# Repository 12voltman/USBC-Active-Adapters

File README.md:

# USBC-Active-Adapters
Active USB-A adapters to USB-C, that don't break spec

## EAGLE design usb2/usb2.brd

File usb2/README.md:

A USB 2.0 only adapter from USB-A male to USB-C female with proper power control based on CC pins. Does not break spec like the passive adapters flooding the market.

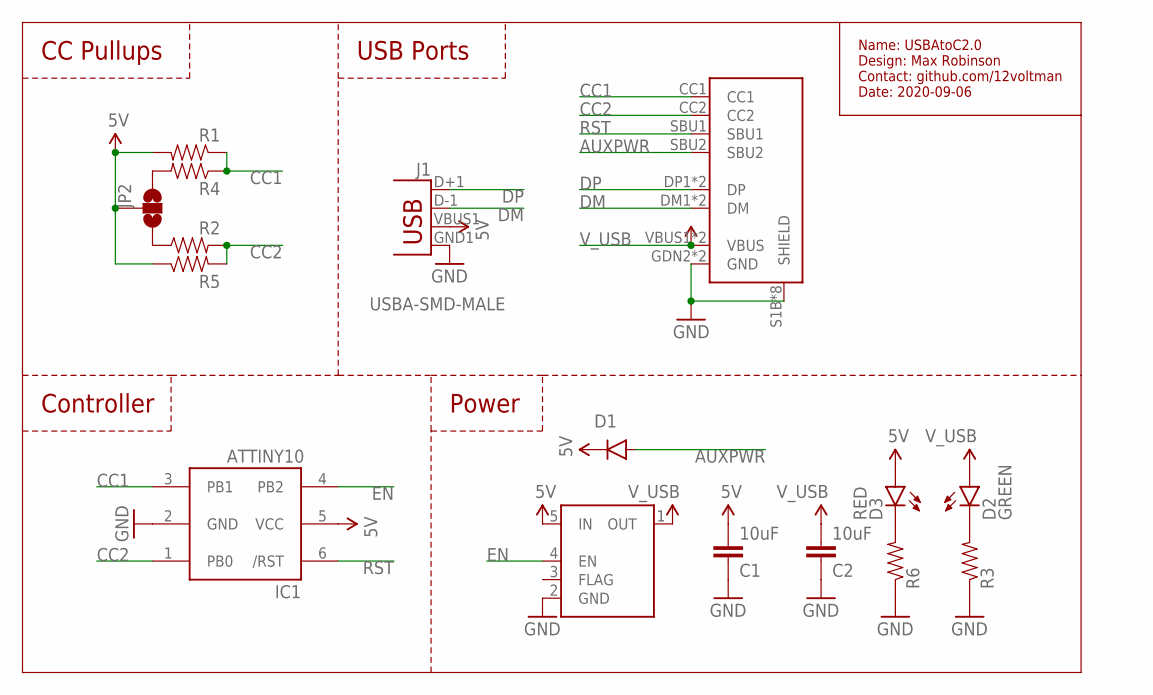
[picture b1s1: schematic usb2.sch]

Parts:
C1, C2: 10uF; 0603-CAP
D1: 250mA/100V; SOD-323
D2: GREEN; LED-0603
D3: RED; LED-0603
IC1: ATTINY10; SOT23-6
J1: USBA-SMD-MALE; USB-A-SMT-MALE
JP2: JUMPER-PAD-3-NOYES_SILK; PAD-JUMPER-3-NO_YES_SILK
R1, R2, R3, R4, R5, R6: RESISTOR0603; 0603-RES
U$1: USB-C_USB2ONLY-OUTLINE; USB-C_12PIN_HORZ-F-OUTLINE
U$2: AP22804/14*W5-7; SOT23-5

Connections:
5V: C1.2, D1.C, D3.A, IC1.5 (VCC), J1.VBUS1 (VBUS), JP2.2, R1.2, R5.1, U$2.5 (IN)
AUXPWR: D1.A, U$1.SBU2
CC1: IC1.3 (PB1), R1.1, R4.1, U$1.CC1
CC2: IC1.1 (PB0), R2.2, R5.2, U$1.CC2
DM: J1.D-1 (D-), U$1.DM1 (DM), U$1.DM2 (DM)
DP: J1.D+1 (D+), U$1.DP1 (DP), U$1.DP2 (DP)
EN: IC1.4 (PB2), U$2.4 (EN)
GND: C1.1, C2.1, IC1.2 (GND), J1.GND1 (GND), R3.1, R6.1, U$1.GDN2 (GND), U$1.GND1 (GND), U$1.S1B (SHIELD), U$1.S1T (SHIELD), U$1.S2B (SHIELD), U$1.S2T (SHIELD), U$1.S3B (SHIELD), U$1.S3T (SHIELD), U$1.S4B (SHIELD), U$1.S4T (SHIELD), U$2.2 (GND)
unnamed: D2.C, R3.2
unnamed: JP2.3, R2.1
unnamed: JP2.1, R4.2
unnamed: D3.C, R6.2
RST: IC1.6 (/RST), U$1.SBU1
V_USB: C2.2, D2.A, U$1.VBUS1 (VBUS), U$1.VBUS2 (VBUS), U$2.1 (OUT)

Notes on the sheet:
Controller
CC Pullups
USB Ports
Power
Name: USBAtoC2.0 Design: Max Robinson Contact: github.com/12voltman Date: 2020-09-06

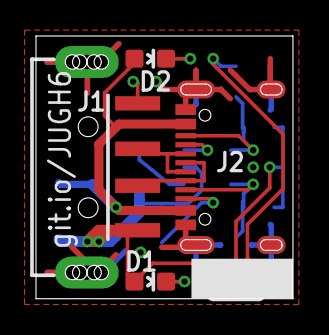
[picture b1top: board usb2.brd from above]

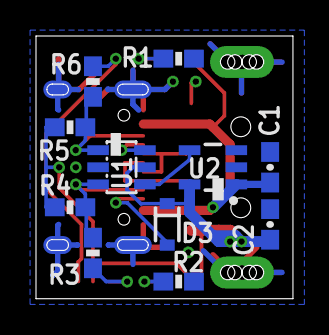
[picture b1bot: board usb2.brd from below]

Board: 2 copper layers, 14.3 x 14.6 mm, 16 parts (11 on the bottom side), 14 nets.

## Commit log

2020-09-06 Initial USB 2.0 files
2020-09-06 Added usb2 schematic image

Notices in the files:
parts and their libraries:
SparkFun-Capacitors: Licensing: Creative Commons ShareAlike 4.0 International - https://creativecommons.org/licenses/by-sa/4.0
